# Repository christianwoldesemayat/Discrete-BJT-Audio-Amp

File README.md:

# 4-Stage Common-Emitter Amplifier: Design, Simulation & PCB (LTspice + KiCad)

An end-to-end analog audio amplifier project, taken from first-principles math all the way to a manufacturable board, using LTspice and KiCad.

**What's inside:**
- Theoretical analysis and hand calculations for each stage
- LTspice simulations and results
- Breadboard prototype with real-world measurements
- Final PCB design in KiCad

## Step 1: Designing the Common-Emitter Input Stage

**Objective:** Design the amplifier's first gain stage using a common-emitter configuration to provide high voltage gain.

**Details:** This phase sets a stable DC operating point, then uses AC small-signal analysis to set the gain and calculate the lower and upper cutoff frequencies that give the stage its band-pass response. The design assumes a transistor current gain of $\beta = 180$ and runs from a ±15 V dual supply. It targets:

- Voltage gain: $|A_v| \geq 30$
- Output swing: 22–24 V peak-to-peak
- Bandwidth covering the full audio range: $f_L \leq 20\ \text{Hz}$ and $f_H \geq 20\ \text{kHz}$

The design is verified in LTspice with operating-point (`.op`), frequency-response (`.ac`), and transient (`.tran`) simulations.

## Step 2: Emitter-Follower Buffer & Multistage Cascade

**Objective:** Add an emitter-follower (EF) buffer stage and expand the design into a multistage cascaded amplifier, preventing loading effects from degrading the gain.

**Details:** To reach a higher overall gain, two common-emitter stages are cascaded and followed by an emitter-follower stage. The follower provides a high input impedance and a low output impedance, so the gain stages aren't loaded down by what comes after them. Inter-stage coupling capacitors are chosen carefully so the cascaded system still covers the full 20 Hz – 20 kHz audio band. The multistage design targets:

- Total voltage gain: $|A_v| \geq 200$
- Maximum output swing: greater than 20 V peak-to-peak
- Power dissipation: below 0.2 W in every resistor

## Step 3: Class AB Output Stage, Component Selection & Full Integration

**Objective:** Design a Class AB push-pull output stage that can drive an 8 Ω speaker, replace the ideal SPICE transistor models with real commercial BJTs, and complete the four-stage amplifier.

**Details:** The final amplifier has four stages: two common-emitter gain stages, an emitter-follower buffer, and a Class AB power output stage. Moving from ideal models to physical components required detailed datasheet analysis, choosing each transistor for its thermal stability, current capability, and transition frequency ($f_T$). The output stage uses a complementary push-pull pair with diode biasing, which keeps both transistors slightly on to minimize crossover distortion. The complete system targets:

- Total voltage gain: $|A_v| > 1000$
- Output power: $\geq 2\ \text{W}$ into an 8 Ω load
- Total power consumption: below 10 W

**Components selected:**

| Stage | Part | Reason |
|---|---|---|
| Input & intermediate gain (CE) | `BC546B` | High $V_{CEO}$ breakdown voltage and consistent current gain |
| Driver / buffer (EF) | `BD139-16` | Thermal stability and medium-power handling |
| Power output (Class AB push-pull) | `BD139` (NPN) & `BD140` (PNP) | Complementary pair for symmetrical push-pull operation |
| Bias network | `1N4148` | Forward voltage sets the output pair's quiescent bias |

## Step 4: Breadboard Prototyping, Measurement & PCB Design

**Objective:** Validate the calculated and simulated design with real hardware, then turn the proven circuit into a printed circuit board (PCB).

**Details:** The complete amplifier is first built on a breadboard to see how it performs with real-world parasitics, thermal drift, and component tolerances. DC offset, voltage gain, output power, and frequency response are measured with an oscilloscope and multimeter. Once the prototype meets its targets, a two-layer PCB is laid out in KiCad. The layout follows these design rules:

- Minimum trace width: 1 mm for power lines and 0.3 mm for signal lines
- Dedicated copper areas for heat sinking the power transistors
- Design Rule Check (DRC) passed with zero errors

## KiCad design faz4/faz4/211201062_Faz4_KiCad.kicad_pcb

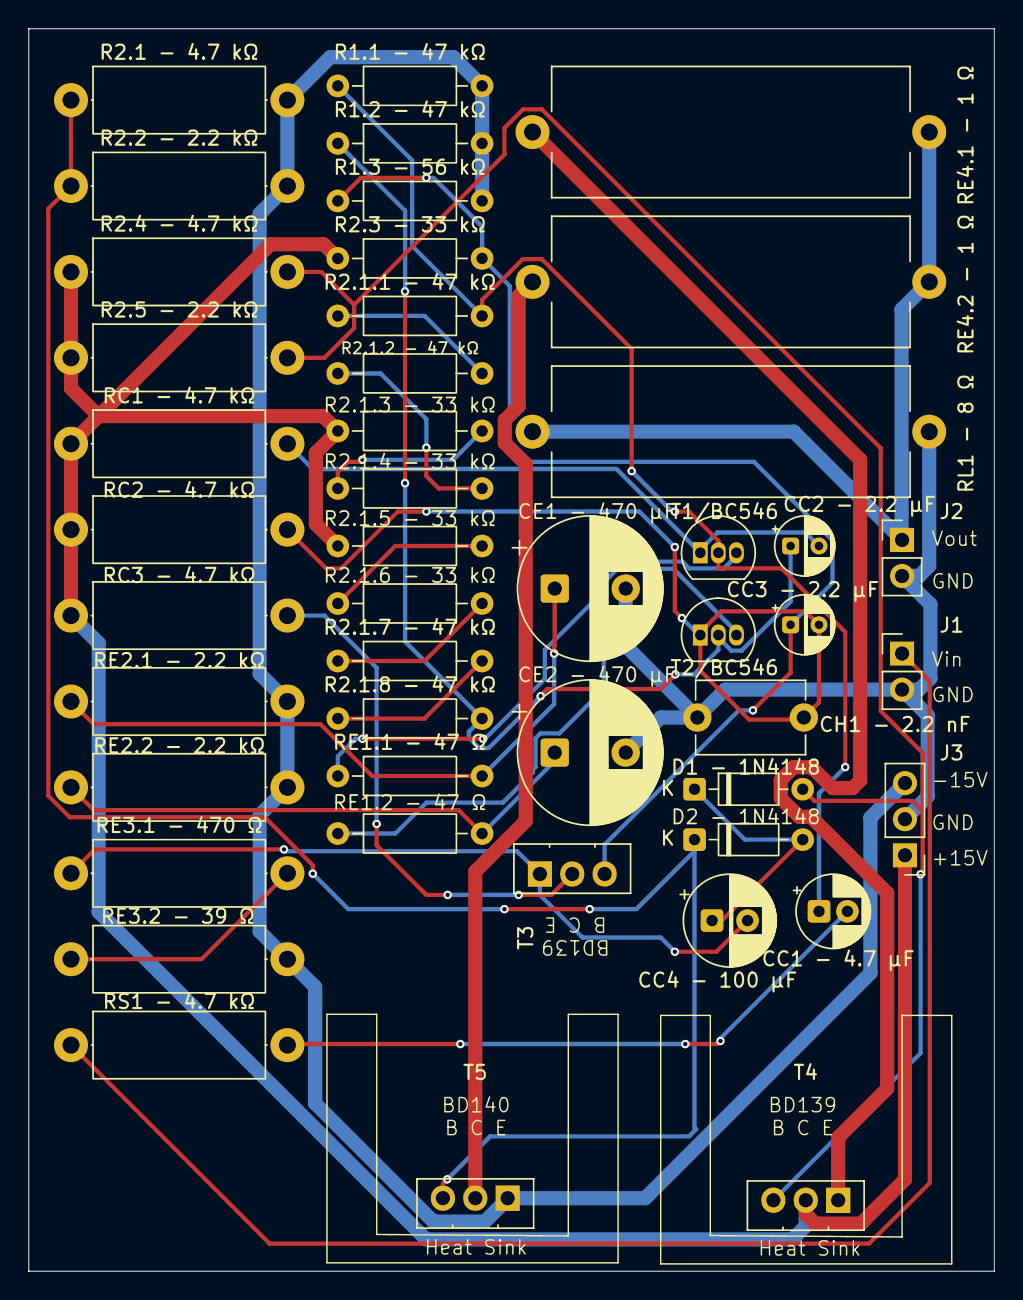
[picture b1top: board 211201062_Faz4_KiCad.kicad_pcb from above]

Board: 2 copper layers, 68.0 x 87.5 mm, 46 parts (0 on the bottom side), 29 nets.

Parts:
CC1 - 4.7 μF: 4.7e-6; CP_Radial_D5.0mm_P2.00mm
CC2 - 2.2 μF, CC3 - 2.2 μF: 2.2e-6; CP_Radial_D4.0mm_P2.00mm
CC4 - 100 μF: 100e-6; CP_Radial_D6.3mm_P2.50mm
CE1 - 470 μF, CE2 - 470 μF: 470e-6; CP_Radial_D10.0mm_P5.00mm
CH1 - 2.2 nF: 2e-9; C_Disc_D7.5mm_W5.0mm_P7.50mm
D1 - 1N4148, D2 - 1N4148: 1N4148; D_DO-35_SOD27_P7.62mm_Horizontal
J1, J2: Conn_01x02; PinHeader_1x02_P2.54mm_Vertical
J3: Conn_01x03; PinHeader_1x03_P2.54mm_Vertical
R1.1 - 47 kΩ, R1.2 - 47 kΩ, R2.1.1 - 47 kΩ, R2.1.2 - 47 kΩ, R2.1.7 - 47 kΩ, R2.1.8 - 47 kΩ: 47e3; R_Axial_DIN0207_L6.3mm_D2.5mm_P10.16mm_Horizontal
R1.3 - 56 kΩ: 56e3; R_Axial_DIN0207_L6.3mm_D2.5mm_P10.16mm_Horizontal
R2.1 - 4.7 kΩ, R2.4 - 4.7 kΩ: 4.7e3; R_Axial_DIN0414_L11.9mm_D4.5mm_P15.24mm_Horizontal
R2.1.3 - 33 kΩ, R2.1.4 - 33 kΩ, R2.1.5 - 33 kΩ, R2.1.6 - 33 kΩ, R2.3 - 33 kΩ: 33e3; R_Axial_DIN0207_L6.3mm_D2.5mm_P10.16mm_Horizontal
R2.2 - 2.2 kΩ, R2.5 - 2.2 kΩ: 2.2e3; R_Axial_DIN0414_L11.9mm_D4.5mm_P15.24mm_Horizontal
RC1 - 4.7 kΩ, RC2 - 4.7 kΩ, RC3 - 4.7 kΩ: 4.7e3; R_Axial_DIN0414_L11.9mm_D4.5mm_P15.24mm_Horizontal
RE1.1 - 47 Ω, RE1.2 - 47 Ω: 47; R_Axial_DIN0207_L6.3mm_D2.5mm_P10.16mm_Horizontal
RE2.1 - 2.2 kΩ, RE2.2 - 2.2 kΩ: 2.2e3; R_Axial_DIN0414_L11.9mm_D4.5mm_P15.24mm_Horizontal
RE3.1 - 470 Ω: 470; R_Axial_DIN0414_L11.9mm_D4.5mm_P15.24mm_Horizontal
RE3.2 - 39 Ω: 39; R_Axial_DIN0414_L11.9mm_D4.5mm_P15.24mm_Horizontal
RE4.1 - 1 Ω, RE4.2 - 1 Ω: 1; R_Axial_Power_L25.0mm_W9.0mm_P27.94mm
RL1 - 8 Ω: 8; R_Axial_Power_L25.0mm_W9.0mm_P27.94mm
RS1 - 4.7 kΩ: 4.7e3; R_Axial_DIN0414_L11.9mm_D4.5mm_P15.24mm_Horizontal
T1/BC546, T2/BC546: BC546; TO-92_Inline
T3, T4: BD139; TO-126-3_Vertical
T5: BD140; TO-126-3_Vertical

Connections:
GND: CE1 - 470 μF.2, CE2 - 470 μF.2, CH1 - 2.2 nF.1, J1.2, J2.2, J3.2, RL1 - 8 Ω.2
unnamed: CC1 - 4.7 μF.2, RS1 - 4.7 kΩ.2
unnamed: CE1 - 470 μF.1, RE1.1 - 47 Ω.2, RE2.1 - 2.2 kΩ.1
unnamed: CE2 - 470 μF.1, RE1.2 - 47 Ω.2, RE2.2 - 2.2 kΩ.1
unnamed: D1 - 1N4148.2 (A), R2.4 - 4.7 kΩ.2, R2.5 - 2.2 kΩ.2, T4.3 (B)
unnamed: CC4 - 100 μF.1, D1 - 1N4148.1 (K), D2 - 1N4148.2 (A)
unnamed: D2 - 1N4148.1 (K), R2.1 - 4.7 kΩ.1, R2.2 - 2.2 kΩ.1, T5.3 (B)
unnamed: J1.1, RS1 - 4.7 kΩ.1
unnamed: J2.1, RE4.1 - 1 Ω.2, RE4.2 - 1 Ω.2, RL1 - 8 Ω.1
unnamed: J3.1, R2.1.3 - 33 kΩ.1, R2.1.5 - 33 kΩ.1, R2.3 - 33 kΩ.1, R2.4 - 4.7 kΩ.1, R2.5 - 2.2 kΩ.1, RC1 - 4.7 kΩ.1, RC2 - 4.7 kΩ.1, RC3 - 4.7 kΩ.1, T4.2 (C)
unnamed: J3.3, R1.1 - 47 kΩ.2, R1.2 - 47 kΩ.2, R1.3 - 56 kΩ.2, R2.1 - 4.7 kΩ.2, R2.2 - 2.2 kΩ.2, RE2.1 - 2.2 kΩ.2, RE2.2 - 2.2 kΩ.2, RE3.2 - 39 Ω.2, T5.1 (E)
unnamed: R2.1.1 - 47 kΩ.1, R2.1.2 - 47 kΩ.2
unnamed: R2.1.2 - 47 kΩ.1, R2.1.4 - 33 kΩ.2
unnamed: R2.1.3 - 33 kΩ.2, R2.1.4 - 33 kΩ.1
unnamed: R2.1.5 - 33 kΩ.2, R2.1.6 - 33 kΩ.1
unnamed: R2.1.6 - 33 kΩ.2, R2.1.7 - 47 kΩ.1
unnamed: R2.1.7 - 47 kΩ.2, R2.1.8 - 47 kΩ.1
unnamed: RE3.1 - 470 Ω.2, RE3.2 - 39 Ω.1
unnamed: CC1 - 4.7 μF.1, R1.1 - 47 kΩ.1, R2.1.1 - 47 kΩ.2, T1/BC546.2 (B)
unnamed: CC2 - 2.2 μF.2, RC1 - 4.7 kΩ.2, T1/BC546.1 (C)
unnamed: RE1.1 - 47 Ω.1, T1/BC546.3 (E)
unnamed: CC2 - 2.2 μF.1, R1.2 - 47 kΩ.1, R2.1.8 - 47 kΩ.2, T2/BC546.2 (B)
unnamed: CC3 - 2.2 μF.2, CH1 - 2.2 nF.2, RC2 - 4.7 kΩ.2, T2/BC546.1 (C)
unnamed: RE1.2 - 47 Ω.1, T2/BC546.3 (E)
unnamed: CC3 - 2.2 μF.1, R1.3 - 56 kΩ.1, R2.3 - 33 kΩ.2, T3.3 (B)
unnamed: RC3 - 4.7 kΩ.2, T3.2 (C)
unnamed: CC4 - 100 μF.2, RE3.1 - 470 Ω.1, T3.1 (E)
unnamed: RE4.1 - 1 Ω.1, T4.1 (E)
unnamed: RE4.2 - 1 Ω.1, T5.2 (C)
